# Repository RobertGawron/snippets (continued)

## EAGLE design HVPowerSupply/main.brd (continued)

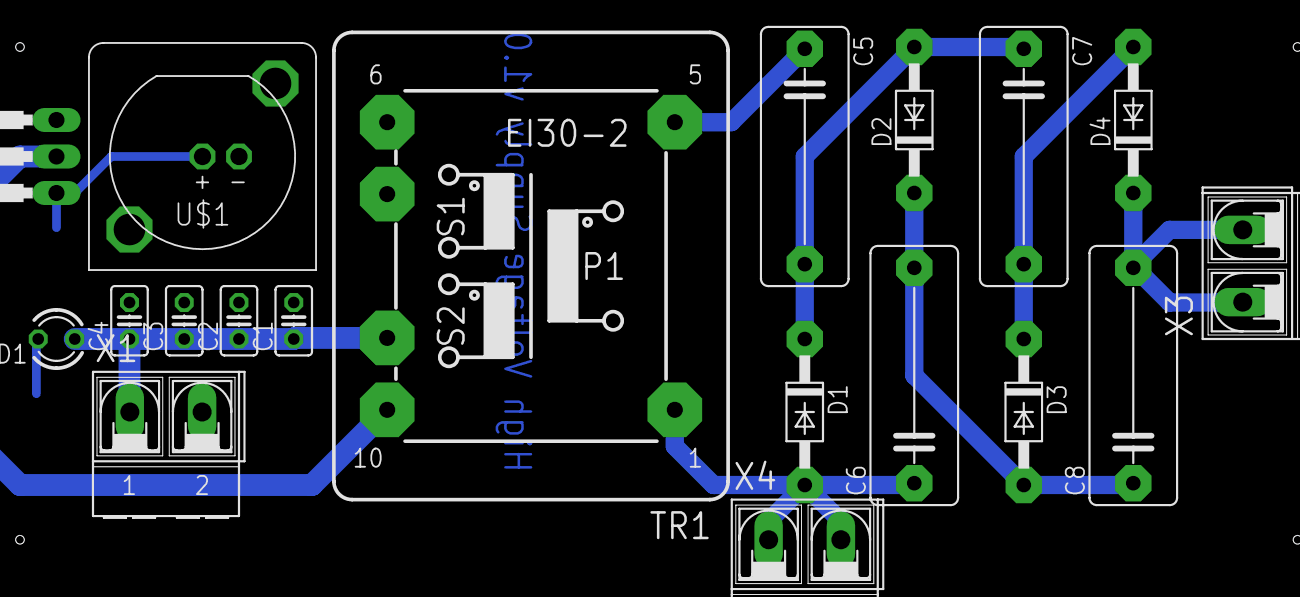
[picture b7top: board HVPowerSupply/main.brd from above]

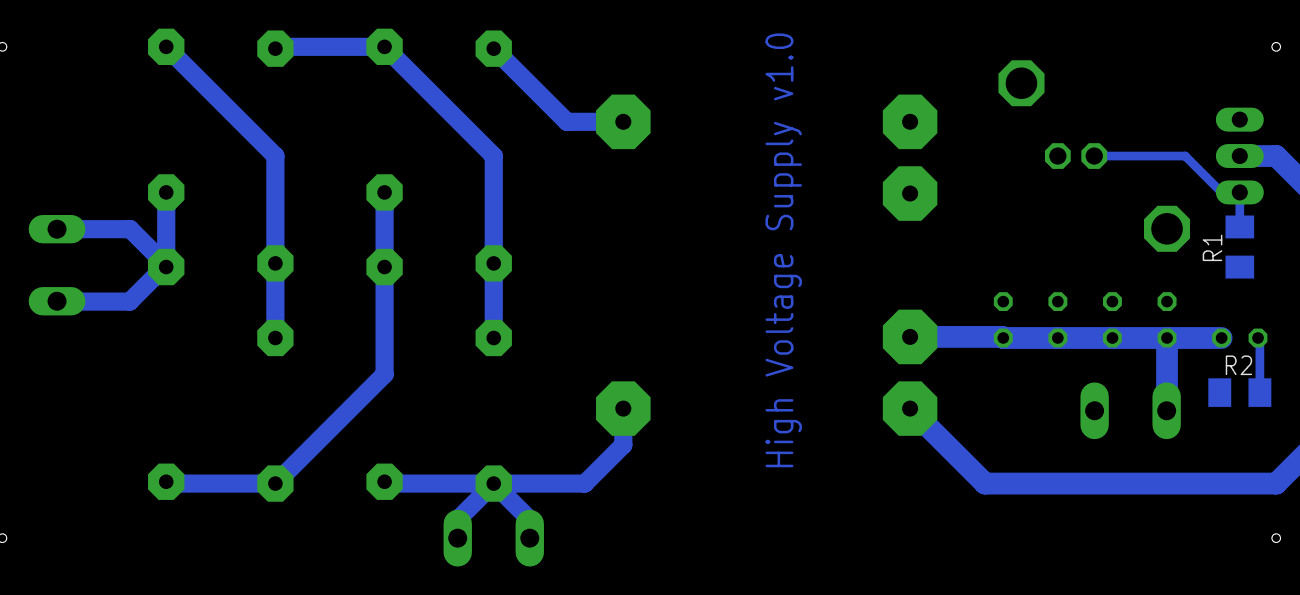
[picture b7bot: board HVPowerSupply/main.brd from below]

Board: 2 copper layers, 21 parts (2 on the bottom side), 11 nets.

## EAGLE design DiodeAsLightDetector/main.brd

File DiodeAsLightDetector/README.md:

# Using regular diode as a photo element.

For more info please visit full article:
http://robertgawron.blogspot.com/2011/04/how-to-use-regular-diode-as-photo.html

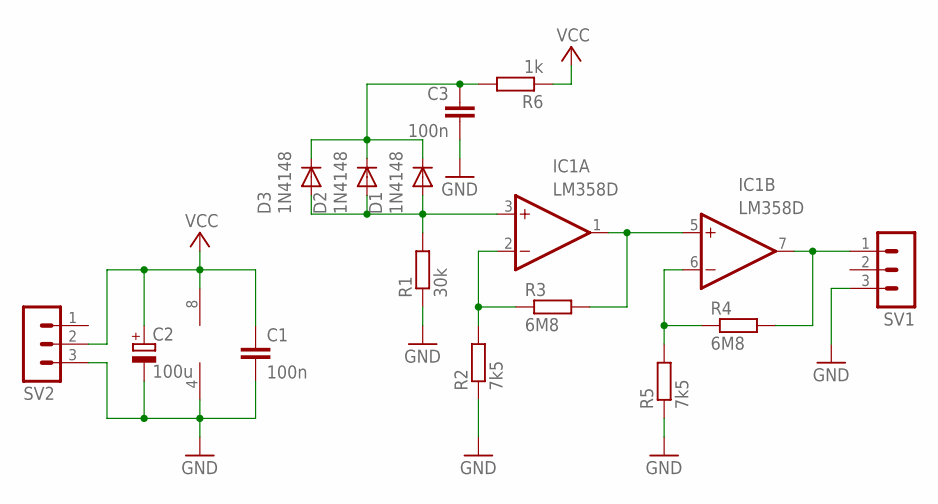
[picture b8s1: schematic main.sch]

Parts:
C1, C3: 100n; C1608
C2: 100u; E2,5-5
D1, D2, D3: 1N4148; DO35-7
IC1: LM358D; SO08
R1: 30k; 0204V
R2, R5: 7k5; 0204V
R3, R4: 6M8; 0204V
R6: 1k; 0204V
SV1, SV2: MA03-1

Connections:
GND: C1.2, C2.-, C3.2, IC1.4 (V-), R1.1, R2.1, R5.1, SV1.3, SV2.3
unnamed: IC1.6 (-IN), R4.1, R5.2
unnamed: IC1.2 (-IN), R2.2, R3.1
unnamed: IC1.1 (OUT), IC1.5 (+IN), R3.2
unnamed: D1.A, D2.A, D3.A, IC1.3 (+IN), R1.2
unnamed: IC1.7 (OUT), R4.2, SV1.1
unnamed: C3.1, D1.C, D2.C, D3.C, R6.2
VCC: C1.1, C2.+, IC1.8 (V+), R6.1, SV2.2

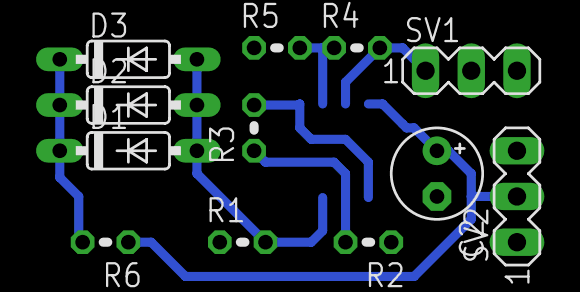
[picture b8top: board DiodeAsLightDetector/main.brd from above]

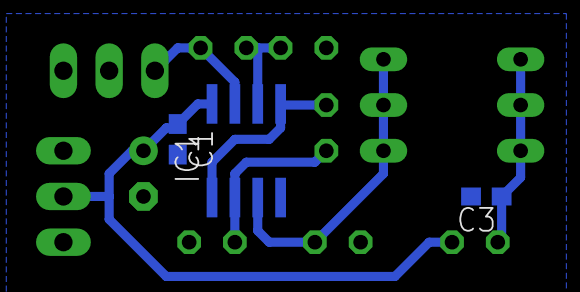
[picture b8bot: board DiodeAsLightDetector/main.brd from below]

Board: 2 copper layers, 15 parts (3 on the bottom side), 8 nets.

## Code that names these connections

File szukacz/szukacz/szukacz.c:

/*
 * szukacz.c
 *
 * Created: 2014-11-17 19:11:55
 *  Author: rgawron
 */ 

#define F_CPU 1000000UL                                    /* Clock Frequency = 1Mhz */

#include <avr/io.h>
#include <util/delay.h>

#define bool_t uint16_t
typedef enum Direction {back, forward, left, right} Direction_t;

bool_t isMovementDetected()
{
	// Movement detected by PIR sensor output in high state
	return (PINB & _BV(PB4));
}

void stopTank()
{
	// set all outputs connected to motor driver to low = no movement
	PORTB &= !(PB0 | PB1 | PB2 | PB3);
}

void goTank(Direction_t direction)
{
	stopTank();
	switch (direction)
	{
		case back:
		break;
		case forward:
			PORTB |= (_BV(PB0) | _BV(PB2));
		break;
		case left:
			PORTB |= _BV(PB2);
		break;
		case right:
		break;	
		default:
			// should not happened
		break;	
	}
}

int main(void)
{
	DDRB = 0b11101111;
	
	int delay = 50000;
	
    while(1)
    {
        stopTank();
		_delay_ms(delay);
        
		if (isMovementDetected())
		{
			goTank(forward);
			_delay_ms(delay);
			goTank(left);	
			_delay_ms(delay);		
		}
	}
}

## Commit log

2011-01-06 files for post about storing image as HTML table added
2011-04-06 removed useless temporary file
2011-04-06 source code for http://robertgawron.blogspot.com/2011/02/hardcoded-images-in-source-of-php.html
2011-04-25 source code for post: http://robertgawron.blogspot.com/2011/04/size-of-files-packed-multiple-times.html
2011-05-02 added README file
2011-05-03 fixed directory structure
2011-05-03 back to the begining, minor changes involved
2011-05-16 added db dump for post about writing CMS entirely in plpgsql
2011-05-16 added code for post about try/catch exception handling in C
2011-05-21 files for further posts
2013-03-02 refactoring, removed poinless classes and changed names from polish to english
2013-03-03 First working version, simplified algorithm, changed containers, removed pointless methods.
2013-03-03 removed poinless directories
2013-03-03 additional scripts moved to a separate directory
2013-03-03 added files for an article about dsl in ruby used to parse assembly files
2013-03-06 final version
2013-03-11 a draft of a captcha breaker script, fixes in directory names of old projects
2014-12-14 cleaning
2014-12-14 Added a template for a project of thermometer (attiny8, 2 x 10 LED).
2014-12-14 Removed redundant files.
2014-12-14 Added a project of a simple robot.
2014-12-20 Moved to a seprate github repository.
2014-12-21 removed junk file.
2014-12-21 Moved to a separate repository.
2014-12-22 Initial version.
2014-12-23 Cleaning.
2014-12-23 Fixed initial commit.
2014-12-23 Fixed directory name.
2014-12-23 ABle to read config and parse files according. The code is a big ball of mess, but hey, it works!
2014-12-23 First working version.
2014-12-24 Junk file removed.
2015-03-07 Updated configuration.
2015-03-07 Added .gitignore
2015-03-07 Removed junks.
2015-03-07 Removed private project files.
2015-03-07 Project renamed.
2015-03-07 Fixed help info.
2015-03-07 I want to have /dist content in the repository.
2015-03-07 Relase file added.
2015-03-29 Circuit and PCB for ionization chamber.
2015-06-18 MiniLabGenerator added.
2015-06-18 Output files added.
2015-06-18 Removed junk projects.
2015-06-18 Remove junk file.
2015-06-21 Fixes after building and testing the prototype.
2015-06-21 Li-Ion charger project.
2015-06-21 Pretty circuit.
2015-06-22 Fixed to be only on one layer.
2015-06-28 Refacotoring of directory structure.
2015-06-28 Rename project directory.
2015-06-28 Renamed project directory.
2015-06-28 Project directory rename.
2015-06-28 Directory for hardware part created.
2015-06-28 README added.
2015-06-28 Weather Station project added.
2015-06-28 Hardware part added.
2015-06-28 Removed README.
2015-06-28 Python3 compatible.
2015-06-28 Smaller sample image.
2015-06-28 CSS rename.
2015-06-28 Script renamed.
2015-06-28 Sample image changed.
2015-06-28 OOP in pure C project added.
2015-07-05 Link to the article.
2015-07-11 SCT2167 used as a LED driver.
2015-07-13 7 Segment LED Display project added.
2015-07-13 Sonar project added.
2015-07-13 Minor layout changes.
2015-07-15 Minor fixes before building the prototype.
2015-07-18 Homemade breadboard project added.
2015-07-18 Using regular diode as a photoellement.
2015-10-24 PCB UV lamp added.
2015-10-24 Banana plug library added.
2015-10-24 Removed falied project.
2015-10-24 Removed failed project.
2015-10-24 HV Power Supply project added.
2015-10-24 Temporary files removed.
2015-10-24 File names changed according to used standard.
2015-10-24 Scripts to anaylze radioactivity added.
2015-11-29 Project added.
2015-11-29 Junks removed.
2016-01-31 Junk projects removed.
2016-03-02 New project added.
2016-03-06 project info added
2016-03-28 New project.
2016-03-29 Fixed element values.
2016-03-29 Fixed capacitor value.
2016-03-29 Fixed electrode layouts.
2016-03-30 Script update.
2016-11-27 Removed obsolete projects and junks.
2016-11-27 New project structure added.
2016-11-27 Initial unfinished version.
2016-11-27 Initial version, PCB not done.
2016-11-27 Power supply done.
2016-11-27 PCB done.
2017-01-06 Second version. Not working.
2017-01-06 Third HW revision, paritialy done.
2017-01-08 Removed obsolete project, PCB fixes.
2018-05-27 Negistor project added.
2018-09-15 project moved to a separate repo
2019-06-09 removed junk files
2019-07-21 remove auto generated files
2019-07-21 documentation cleanup
2019-07-21 documentation update
2019-07-21 project description update
2019-07-21 remove obsolete files
2020-11-06 Fix grammar mistakes (found by Code Spell Checker add-on in VSCode). (fix #20)
